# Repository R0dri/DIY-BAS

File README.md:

# DIY - Biosignals Adquisition System with high quality of data adquisition and extremly low cost
This is a DIY EEG device with high quality of the data adquisition, made for research

The data adquisition is made through a Teensy 3.2 board using its 16 bit ADC converters for a good quality. The data is sent through serial com to a raspberry pi 3 for ICA analysis of the data.

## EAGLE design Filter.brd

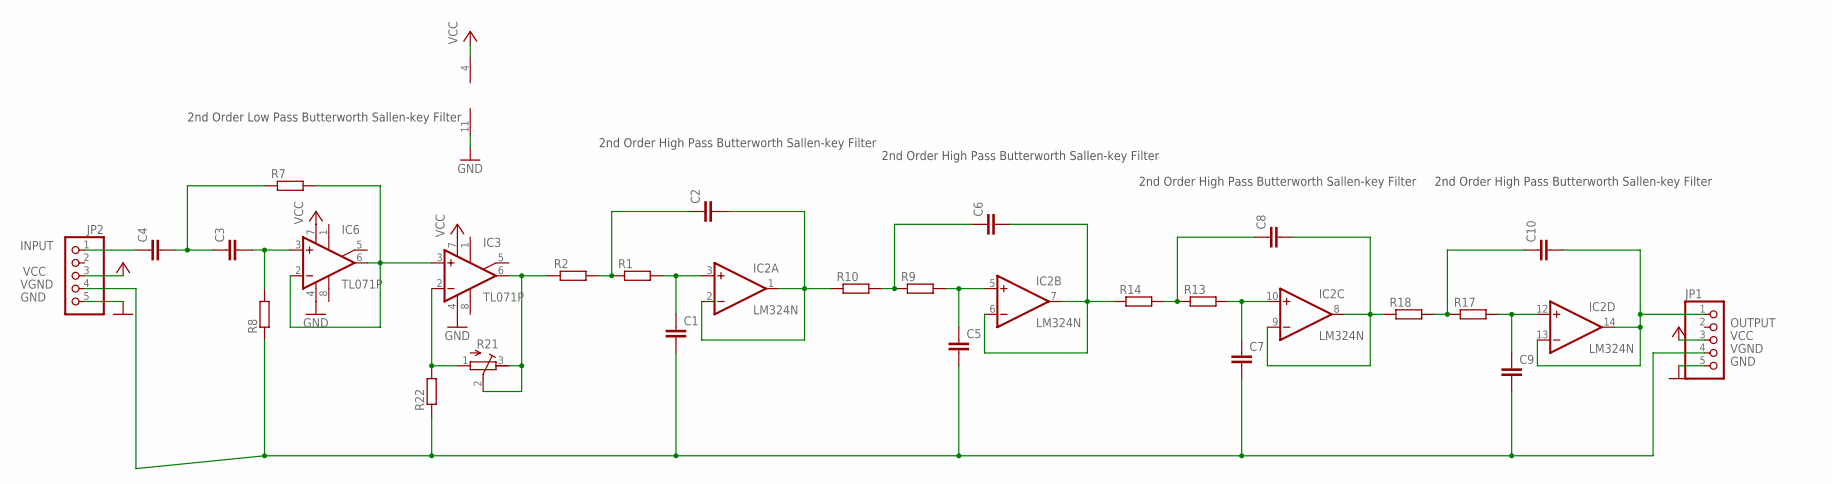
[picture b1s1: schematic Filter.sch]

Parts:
C1, C2, C3, C4, C5, C6, C7, C8, C9, C10: C2.5/2; C2.5-2
IC2: LM324N; DIL14
IC3, IC6: TL071P; DIL08
JP1, JP2: PINHD-1X5; 1X05
R1, R2, R7, R8, R9, R13, R14, R17, R22: R0204/7; 0204/7
R10, R18: R0207/10; 0207/10
R21: R-TRIMM3299W; RTRIM3299W

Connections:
GND: IC2.11 (V-), IC3.4 (V-), IC6.4 (V-), JP1.5, JP2.5
INPUT: C4.1, JP2.1
unnamed: C2.1, R1.1, R2.2
unnamed: C1.1, IC2.3 (+IN), R1.2
unnamed: C2.2, IC2.1 (OUT), IC2.2 (-IN), R10.1
unnamed: IC3.6 (OUT), R2.1, R21.2 (S), R21.3 (E)
unnamed: C3.1, C4.2, R7.1
unnamed: C6.1, R9.1, R10.2
unnamed: C3.2, IC6.3 (+IN), R8.2
unnamed: IC3.3 (+IN), IC6.2 (-IN), IC6.6 (OUT), R7.2
unnamed: C6.2, IC2.6 (-IN), IC2.7 (OUT), R14.1
unnamed: C5.1, IC2.5 (+IN), R9.2
unnamed: C8.1, R13.1, R14.2
unnamed: C8.2, IC2.8 (OUT), IC2.9 (-IN), R18.1
unnamed: C7.1, IC2.10 (+IN), R13.2
unnamed: C10.1, R17.1, R18.2
unnamed: C9.1, IC2.12 (+IN), R17.2
unnamed: IC3.2 (-IN), R21.1 (A), R22.2
OUTPUT: C10.2, IC2.13 (-IN), IC2.14 (OUT), JP1.1
VCC: IC2.4 (V+), IC3.7 (V+), IC6.7 (V+), JP1.3, JP2.3
VGND: C1.2, C5.2, C7.2, C9.2, JP1.4, JP2.4, R8.1, R22.1

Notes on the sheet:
2nd Order Low Pass Butterworth Sallen-key Filter
2nd Order High Pass Butterworth Sallen-key Filter

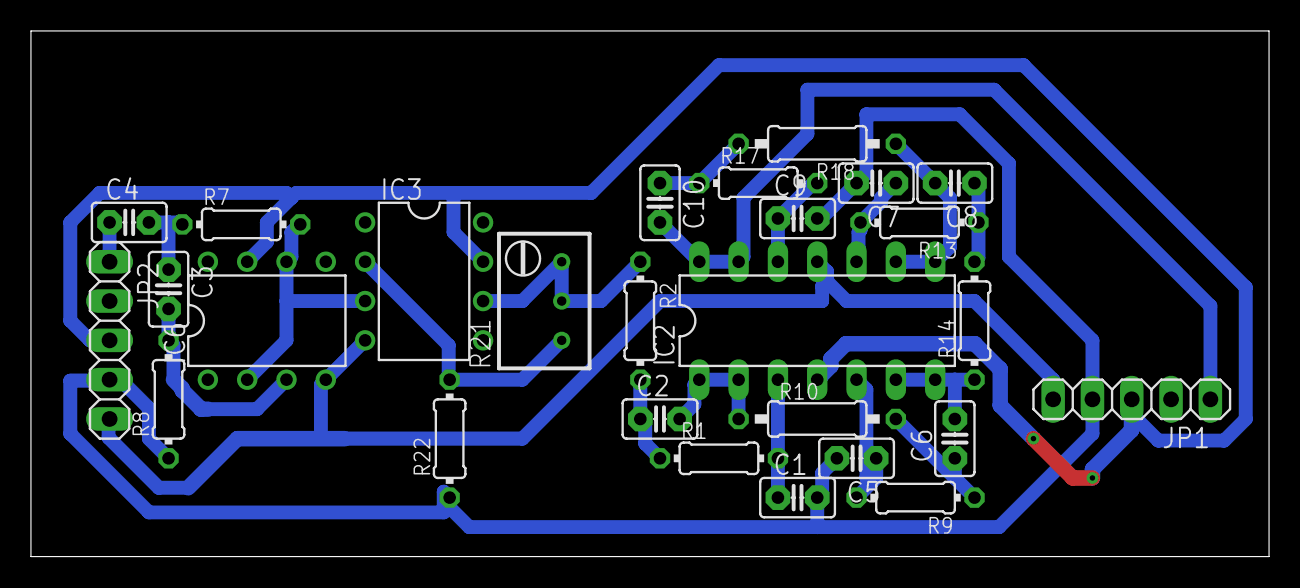
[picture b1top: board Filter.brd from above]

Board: 2 copper layers, 80.0 x 34.0 mm, 27 parts (0 on the bottom side), 21 nets.

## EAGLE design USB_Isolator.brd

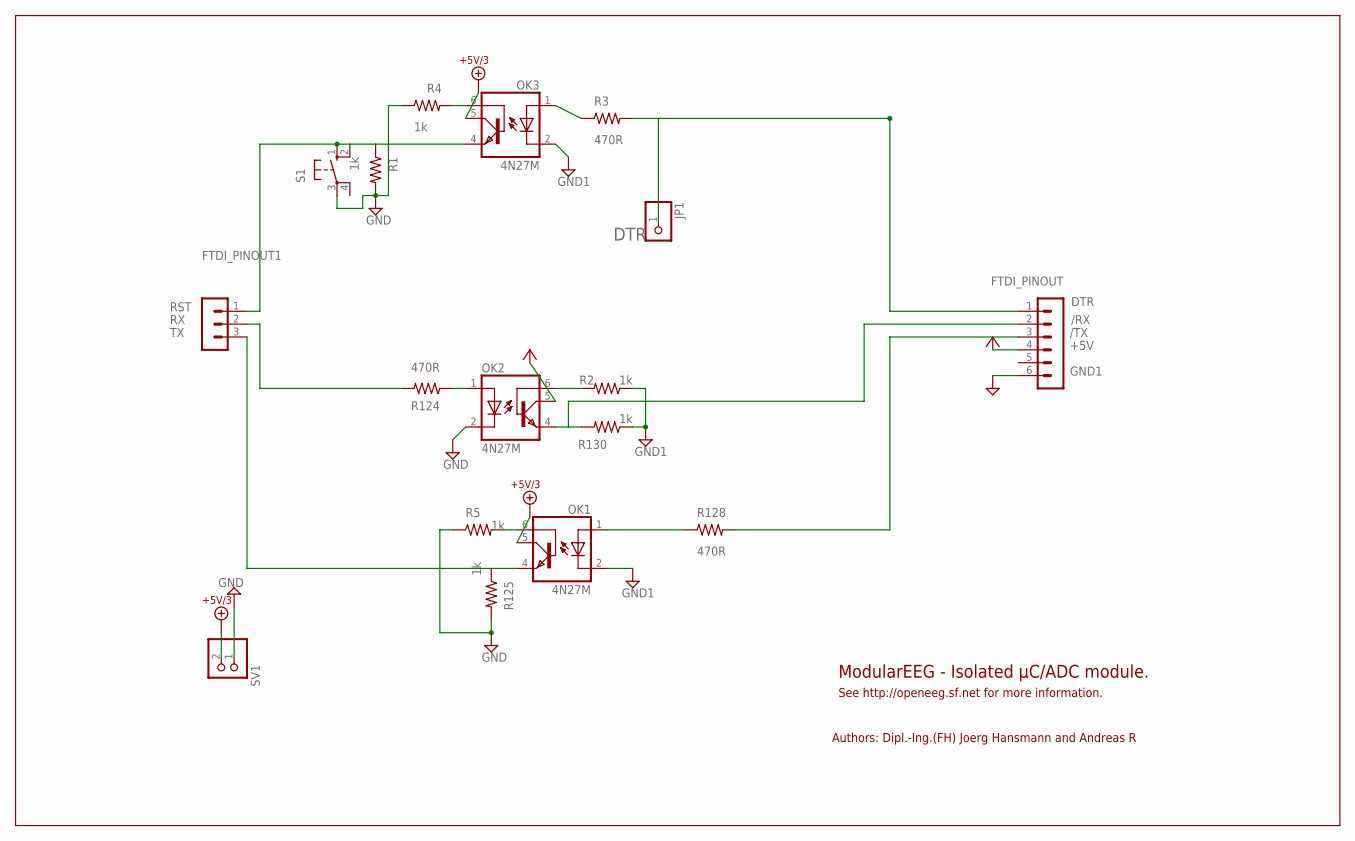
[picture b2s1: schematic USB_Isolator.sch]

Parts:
FTDI_PINOUT: MA06-1
FTDI_PINOUT1: MA03-1
JP1: PINHD-1X1; 1X01
OK1, OK2, OK3: 4N27M; DIL06
R1, R5, R125: 1k; 0204/5
R2, R130: 1k; 0204/7
R3, R124, R128: 470R; 0204/7
R4: 1k; 0204V
S1: 10-XX; B3F-10XX
SV1: PINHD-1X2; 1X02

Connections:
+5V: FTDI_PINOUT.4, OK2.5 (COL)
+5V/3: OK1.5 (COL), OK3.5 (COL), SV1.2
/RX: FTDI_PINOUT.2, OK2.4 (EMI), R130.2
/TX: FTDI_PINOUT.3, R128.2
DTR: FTDI_PINOUT.1, JP1.1, R3.2
GND: OK2.2 (C), R1.2, R4.1, R5.1, R125.2, S1.3, SV1.1
GND1: FTDI_PINOUT.6, OK1.2 (C), OK3.2 (C), R2.1, R130.1
unnamed: OK3.1 (A), R3.1
unnamed: OK2.6 (BAS), R2.2
unnamed: OK3.6 (BAS), R4.2
unnamed: OK1.6 (BAS), R5.2
unnamed: OK2.1 (A), R124.1
unnamed: OK1.1 (A), R128.1
RST: FTDI_PINOUT1.1, OK3.4 (EMI), R1.1, S1.1 (S), S1.2 (S1)
RX: FTDI_PINOUT1.2, R124.2
TX: FTDI_PINOUT1.3, OK1.4 (EMI), R125.1

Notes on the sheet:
Authors: Dipl.-Ing.(FH) Joerg Hansmann and Andreas R
ModularEEG - Isolated µC/ADC module.
See http://openeeg.sf.net for more information.

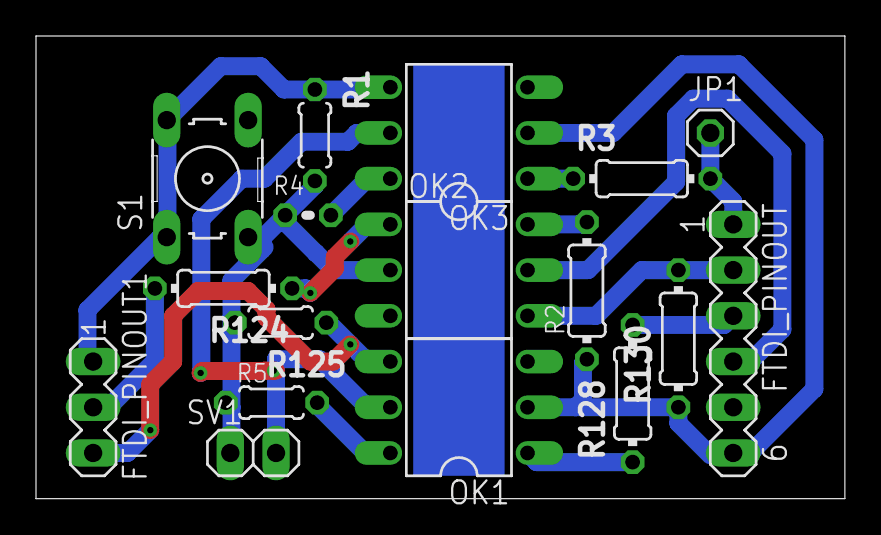
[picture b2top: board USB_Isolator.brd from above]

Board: 2 copper layers, 44.9 x 25.7 mm, 17 parts (0 on the bottom side), 16 nets.

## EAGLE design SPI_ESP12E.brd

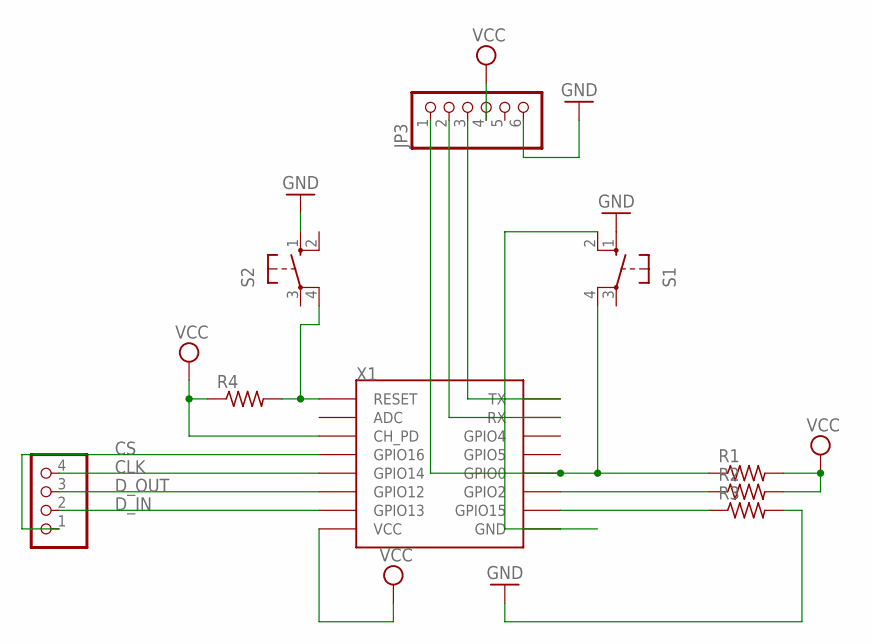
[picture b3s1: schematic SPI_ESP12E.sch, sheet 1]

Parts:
JP3: PINHD-1X6B; 1X06-BIG
R1, R2, R3: R-US_0204/7; 0204/7
R4: R-US_0204/5; 0204/5
S1, S2: 10-XX; B3F-10XX
SPI: PINHD-1X4; 1X04
X1: ESP12SMD; ESP12-SMD

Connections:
CLK: SPI.4, X1.GPIO14
CS: SPI.1, X1.GPIO16
D_IN: SPI.2, X1.GPIO13
D_OUT: SPI.3, X1.GPIO12
GND: JP3.6, R3.2, S1.1 (S), S2.1 (S)
unnamed: R3.1, X1.GPIO15
unnamed: S1.2 (S1), X1.GND
unnamed: R2.1, X1.GPIO2
unnamed: R4.2, S2.4 (P1), X1.RESET
unnamed: JP3.1, R1.1, S1.4 (P1), X1.GPIO0
unnamed: JP3.3, X1.TXD0 (TX)
unnamed: JP3.2, X1.RXD0 (RX)
VCC: JP3.4, R1.2, R2.2, R4.1, X1.CH_PD, X1.VCC

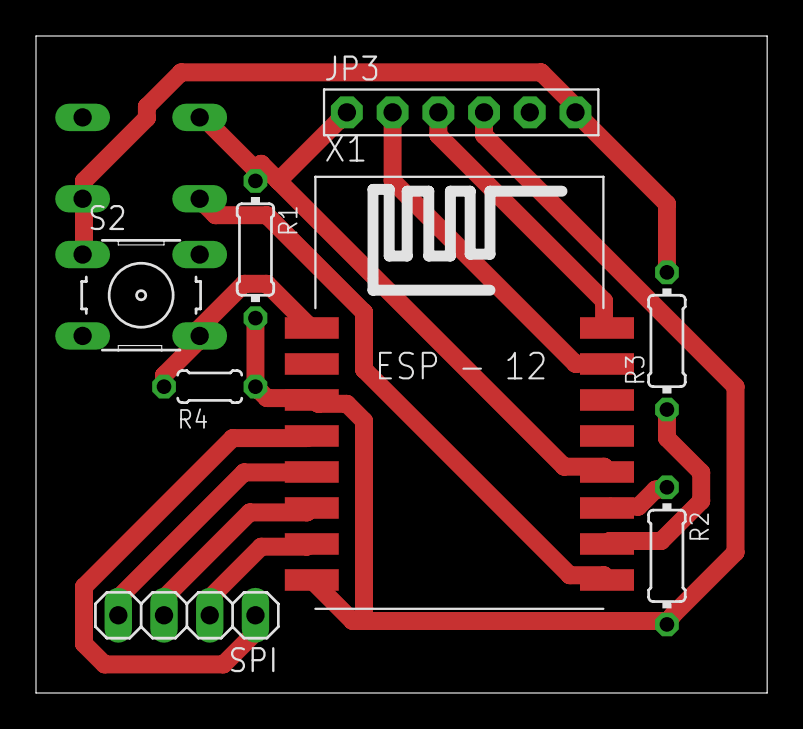
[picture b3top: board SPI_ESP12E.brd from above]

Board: 2 copper layers, 40.6 x 36.5 mm, 9 parts (1 on the bottom side), 13 nets.

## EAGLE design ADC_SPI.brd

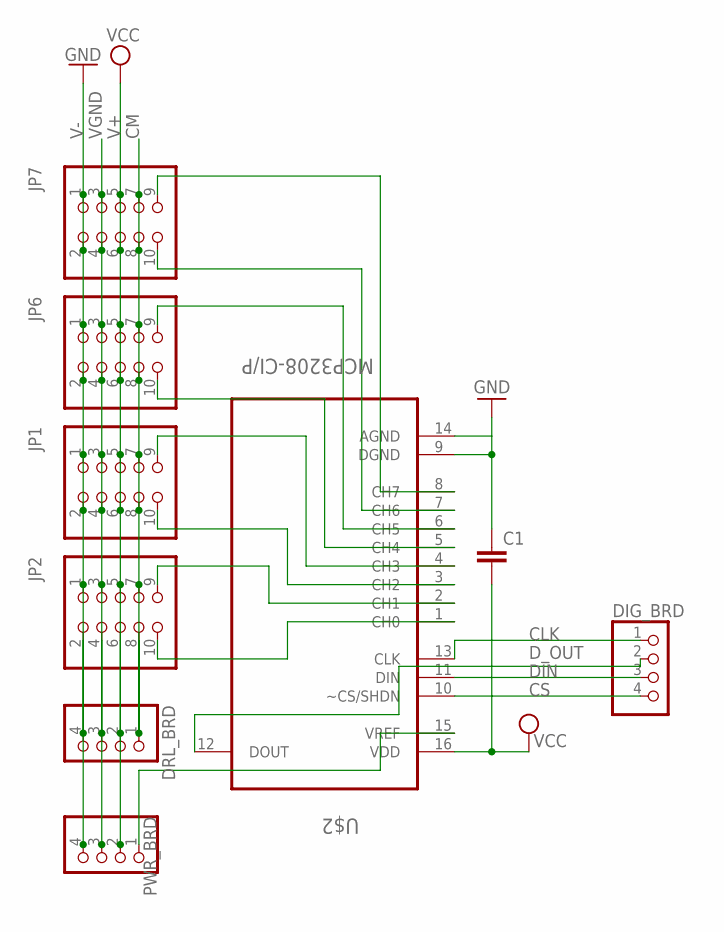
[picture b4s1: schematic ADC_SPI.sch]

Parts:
C1: C2.5/2; C2.5-2
DIG_BRD: PINHD-1X4; 1X04
DRL_BRD: PINHD-1X4; 1X04
JP1, JP2, JP6, JP7: PINHD-2X5; 2X05
PWR_BRD: PINHD-1X4; 1X04
U$2: MCP3208-CI/P; DIP254P762X432-16

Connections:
CLK: DIG_BRD.1, U$2.13 (CLK)
CM: DRL_BRD.1, JP1.7, JP1.8, JP2.7, JP2.8, JP6.7, JP6.8, JP7.7, JP7.8
CS: DIG_BRD.4, U$2.10 (~CS/SHDN)
DIN: DIG_BRD.3, U$2.11 (DIN)
D_OUT: DIG_BRD.2, U$2.12 (DOUT)
GND: C1.1, U$2.9 (DGND), U$2.14 (AGND)
unnamed: JP2.10, U$2.1 (CH0)
unnamed: PWR_BRD.1, U$2.15 (VREF)
unnamed: JP7.9, U$2.8 (CH7)
unnamed: JP7.10, U$2.7 (CH6)
unnamed: JP6.9, U$2.6 (CH5)
unnamed: JP6.10, U$2.5 (CH4)
unnamed: JP1.9, U$2.4 (CH3)
unnamed: JP1.10, U$2.3 (CH2)
unnamed: JP2.9, U$2.2 (CH1)
V+: DRL_BRD.2, JP1.5, JP1.6, JP2.5, JP2.6, JP6.5, JP6.6, JP7.5, JP7.6, PWR_BRD.2
V-: DRL_BRD.4, JP1.1, JP1.2, JP2.1, JP2.2, JP6.1, JP6.2, JP7.1, JP7.2, PWR_BRD.4
VCC: C1.2, U$2.16 (VDD)
VGND: DRL_BRD.3, JP1.3, JP1.4, JP2.3, JP2.4, JP6.3, JP6.4, JP7.3, JP7.4, PWR_BRD.3

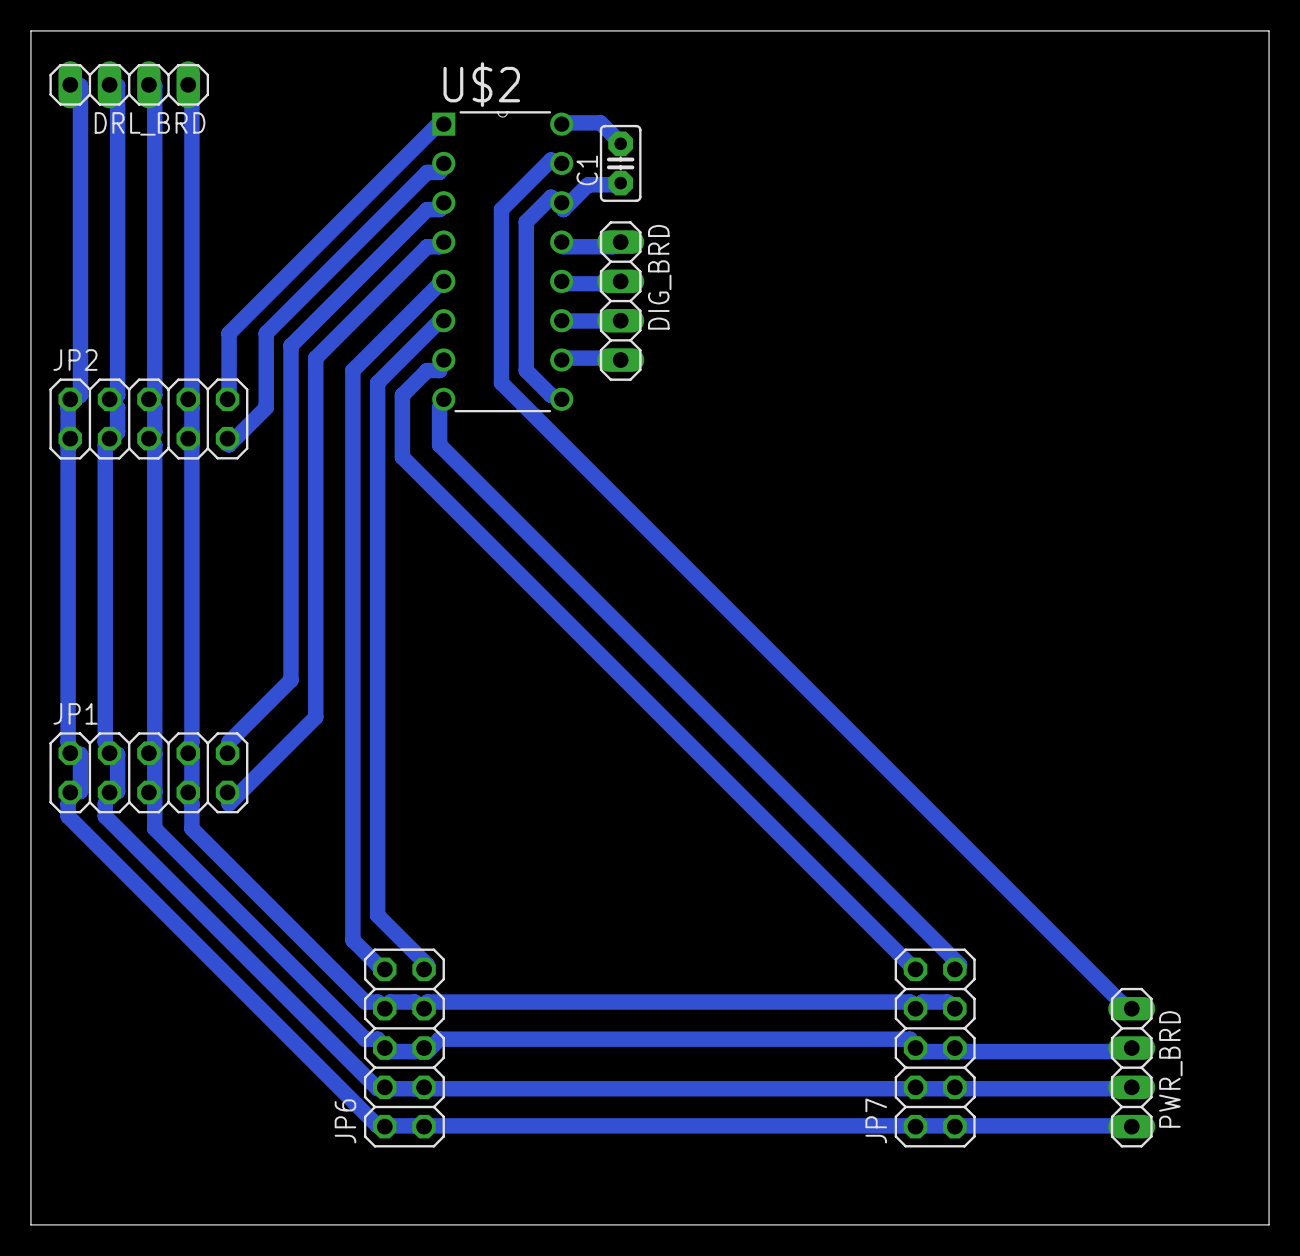
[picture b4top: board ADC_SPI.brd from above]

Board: 2 copper layers, 80.0 x 77.1 mm, 9 parts (0 on the bottom side), 19 nets.

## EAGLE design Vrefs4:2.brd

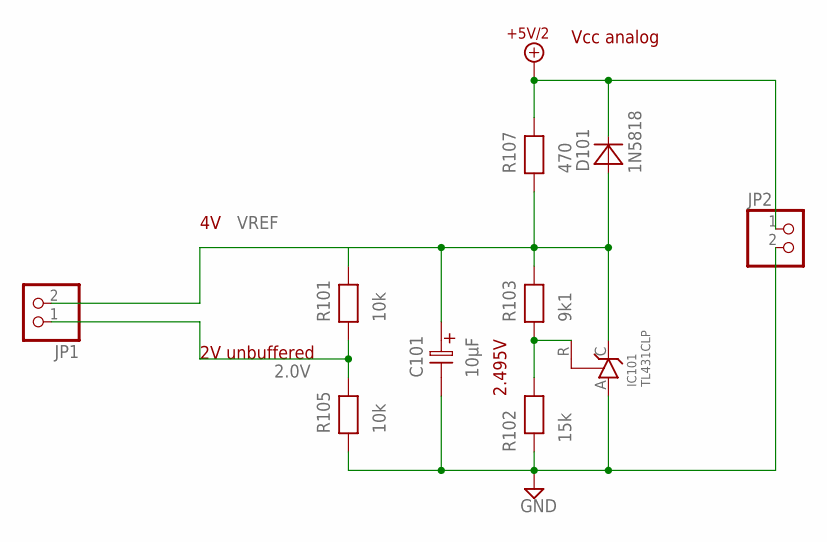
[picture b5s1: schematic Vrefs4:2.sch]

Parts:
C101: 10µF; EL25B
D101: 1N5818; D-10
IC101: TL431CLP; TO92-CLP
JP1, JP2: PINHD-1X2; 1X02
R101, R105: 10k; R-10
R102: 15k; R-10
R103: 9k1; R-10
R107: 470; R-10

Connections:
2.0V: JP1.1, R101.1, R105.2
+5V/2: D101.2 (K), JP2.1, R107.2
GND: C101.2, IC101.A, JP2.2, R102.1, R105.1
unnamed: IC101.R, R102.2, R103.1
VREF: C101.1, D101.1 (A), IC101.C, JP1.2, R101.2, R103.2, R107.1

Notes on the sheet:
2.495V
2V unbuffered
Vcc analog

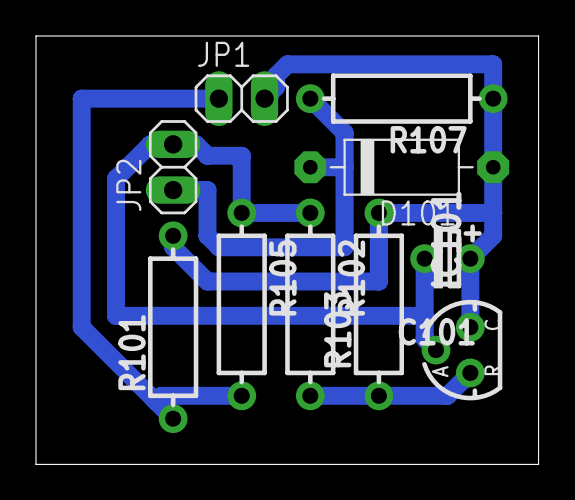
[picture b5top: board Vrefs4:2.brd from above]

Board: 2 copper layers, 27.9 x 23.8 mm, 10 parts (0 on the bottom side), 5 nets.

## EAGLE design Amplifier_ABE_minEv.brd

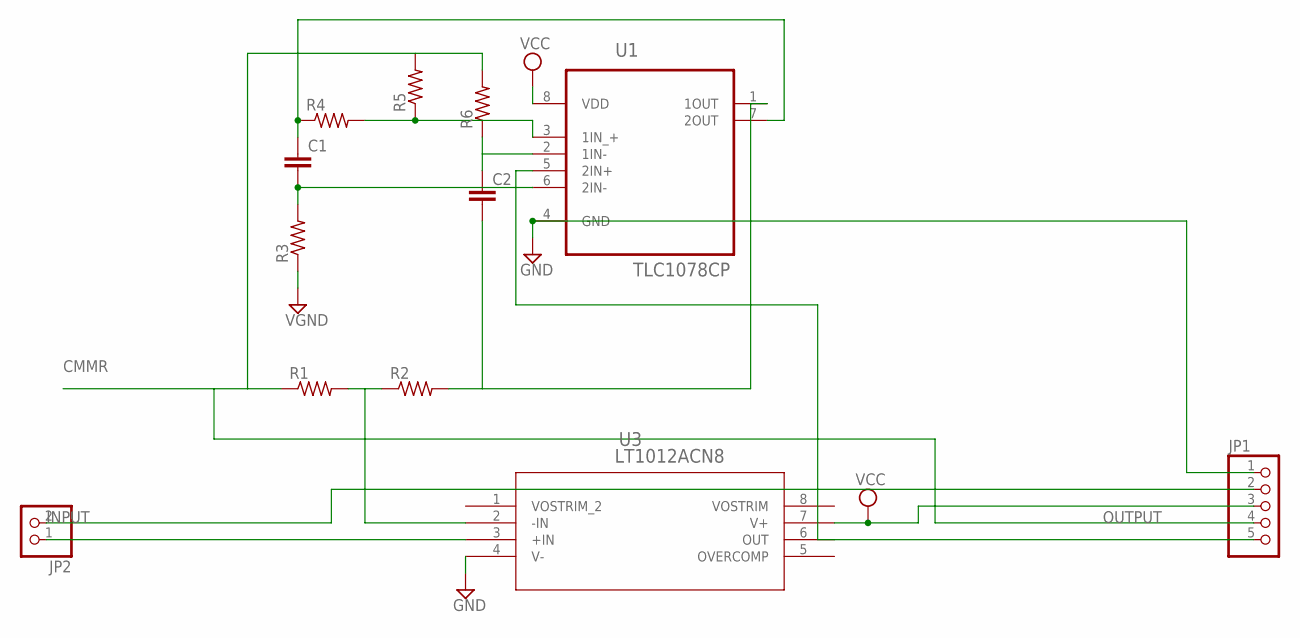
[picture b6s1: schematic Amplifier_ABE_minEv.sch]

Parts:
C1, C2: C-EU025-024X044; C025-024X044
JP1: PINHD-1X5; 1X05
JP2: PINHD-1X2; 1X02
R1, R2, R4, R5: R-US_0204/7; 0204/7
R3, R6: R-US_0204/5; 0204/5
U1: TLC1078CP; DIP254P762X508-8
U3: LT1012ACN8; LT1012ACN8_PDIP-8_N

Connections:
CMMR: JP1.4, R1.1, R5.2, R6.2
GND: JP1.1, R3.1, U1.4 (GND), U3.4 (V-)
INPUT: JP2.1, U3.3 (+IN)
unnamed: R1.2, R2.1, U3.2 (-IN)
unnamed: JP1.2, JP2.2
unnamed: C2.2, R2.2, U1.1 (1OUT)
unnamed: C1.2, R3.2, U1.6 (2IN-)
unnamed: C1.1, R4.1, U1.7 (2OUT)
unnamed: R4.2, R5.1, U1.3 (1IN_+)
unnamed: C2.1, R6.1, U1.2 (1IN-)
OUTPUT: JP1.5, U1.5 (2IN+), U3.6 (OUT)
VCC: JP1.3, U1.8 (VDD), U3.7 (V+)

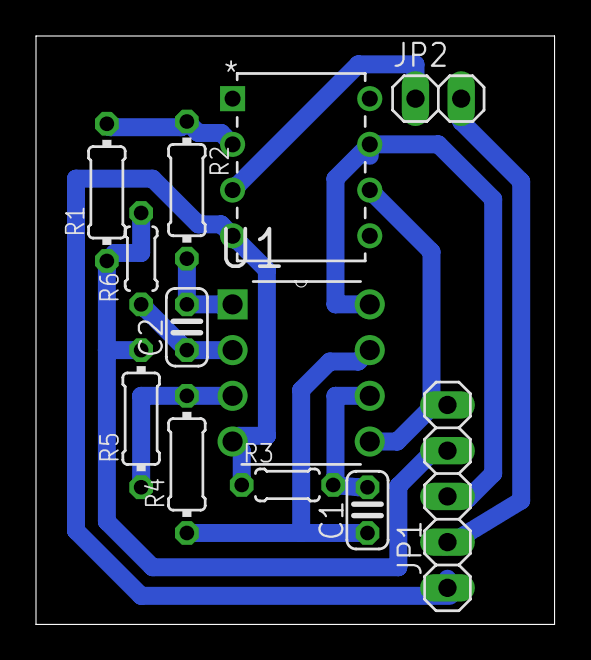
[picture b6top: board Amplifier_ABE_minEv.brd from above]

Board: 2 copper layers, 28.8 x 32.7 mm, 12 parts (0 on the bottom side), 12 nets.

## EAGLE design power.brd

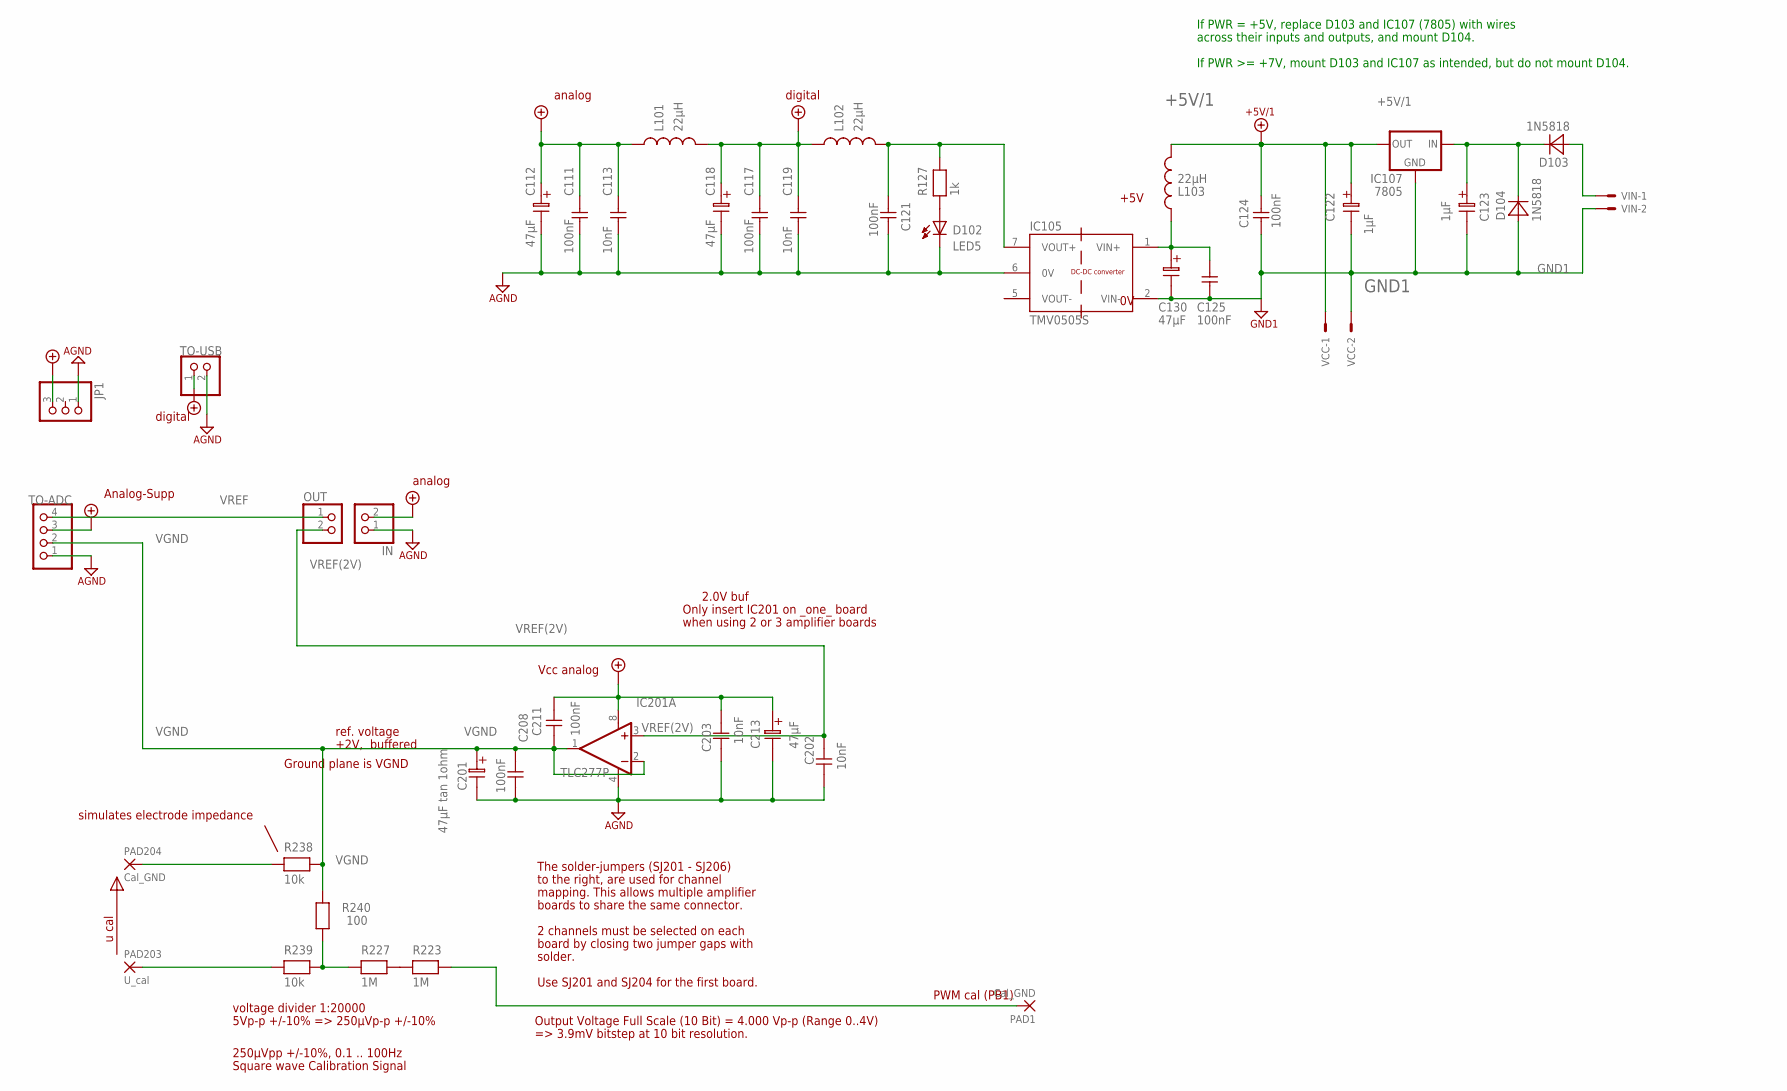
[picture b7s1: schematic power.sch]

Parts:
C111, C117, C125, C208, C211: 100nF; C-5
C112, C118, C130, C213: 47µF; EL25B
C113, C119, C202, C203: 10nF; C-5
C121, C124: 100nF; C-5@1
C122, C123: 1µF; EL25B
C201: 47µF tan 1ohm; EL25B
D102: LED5
D103, D104: 1N5818; D-12,5
IC105: TMV0505S; MEJDCDC-SC
IC107: 7805; 78XXL_S
IC201: TLC277P; DIL-08
IN: PINHD-1X2; 1X02
JP1: PINHD-1X3; 1X03
L101, L102, L103: 22µH; R-12,5
OUT: PINHD-1X2; 1X02
PAD1, PAD204: Cal_GND; WIREPAD1
PAD203: U_cal; WIREPAD1
R127: 1k; R-10
R223, R227: 1M; R-10
R238, R239: 10k; R-10
R240: 100; R-10
TO-ADC: PINHD-1X4; 1X04
TO-USB: PINHD-1X2; 1X02
VCC: 87758-0216
VIN: 22-23-2021

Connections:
+5V/1: C122.1, C124.2, IC107.OUT, L103.2, VCC.1
+6TO12V: C123.1, D103.2 (K), D104.2 (K), IC107.IN
A-VCC: C111.2, C112.1, C113.2, C203.1, C211.2, C213.1, IC201.8 (V+), IN.2, L101.1, TO-ADC.3
D-VCC: C117.2, C118.1, C119.2, JP1.3, L101.2, L102.1, TO-USB.1
GND: C111.1, C112.2, C113.1, C117.1, C118.2, C119.1, C121.2, C201.2, C202.2, C203.2, C208.2, C213.2, D102.K, IC105.6 (0V), IC201.4 (V-), IN.1, JP1.1, TO-ADC.1, TO-USB.2
GND1: C122.2, C123.2, C124.1, C125.1, C130.2, D104.1 (A), IC105.2 (VIN-), IC107.GND, VCC.2, VIN.2
unnamed: C121.1, IC105.7 (VOUT+), L102.2, R127.2
unnamed: D102.A, R127.1
unnamed: D103.1 (A), VIN.1
unnamed: PAD204.1, R238.1
unnamed: R227.1, R239.2, R240.2
unnamed: C125.2, C130.1, IC105.1 (VIN+), L103.1
unnamed: R223.1, R227.2
unnamed: PAD203.1, R239.1
PWM: PAD1.1, R223.2
VGND: C201.1, C208.1, C211.1, IC201.1 (OUT), IC201.2 (-IN), R238.2, R240.1, TO-ADC.2
VOUT-: IC105.5 (VOUT-)
VREF: OUT.1, TO-ADC.4
VREF(2V): C202.1, IC201.3 (+IN), OUT.2

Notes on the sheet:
+5V
analog
digital
If PWR = +5V, replace D103 and IC107 (7805) with wires
If PWR >= +7V, mount D103 and IC107 as intended, but do not mount D104.
across their inputs and outputs, and mount D104.
ref. voltage
+2V, buffered
u cal
Output Voltage Full Scale (10 Bit) = 4.000 Vp-p (Range 0..4V)
Vcc analog
2.0V buf
PWM cal (PB1)
250µVpp +/-10%, 0.1 .. 100Hz
Square wave Calibration Signal
voltage divider 1:20000
simulates electrode impedance
Ground plane is VGND
5Vp-p +/-10% => 250µVp-p +/-10%
when using 2 or 3 amplifier boards
Only insert IC201 on _one_ board
The solder-jumpers (SJ201 - SJ206)
boards to share the same connector.
2 channels must be selected on each
solder.
to the right, are used for channel
mapping. This allows multiple amplifier
=> 3.9mV bitstep at 10 bit resolution.
board by closing two jumper gaps with
Use SJ201 and SJ204 for the first board.
Analog-Supp

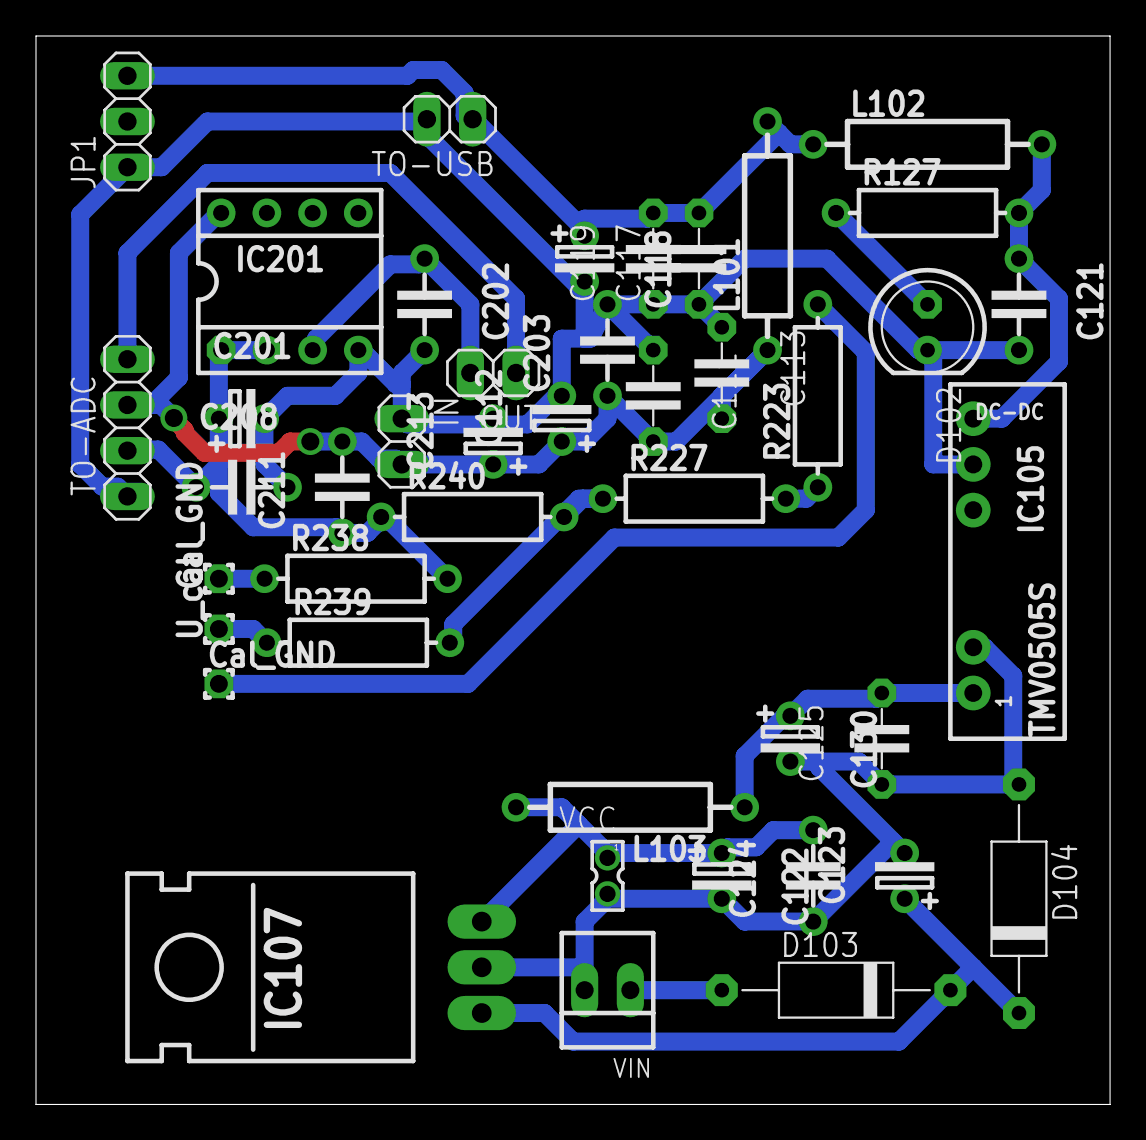
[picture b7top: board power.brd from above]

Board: 2 copper layers, 59.7 x 59.4 mm, 43 parts (0 on the bottom side), 18 nets.

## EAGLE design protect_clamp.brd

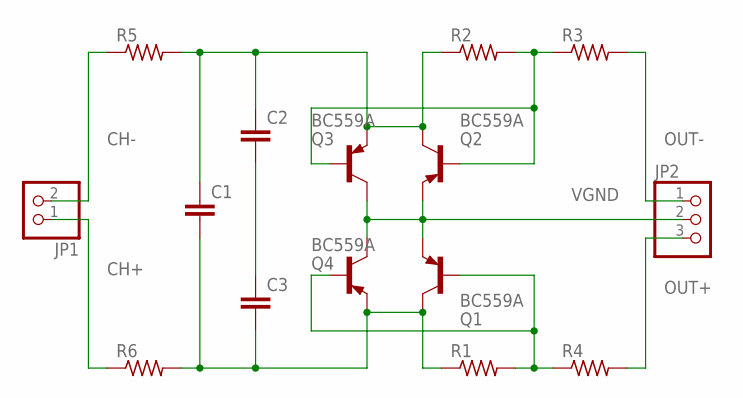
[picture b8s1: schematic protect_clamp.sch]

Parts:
C1, C2, C3: C2.5/2; C2.5-2
JP1: PINHD-1X2; 1X02
JP2: PINHD-1X3; 1X03
Q1, Q2, Q3, Q4: BC559A; TO92-EBC
R1, R2, R3, R4, R5, R6: R-US_0204/5; 0204/5

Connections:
CH+: JP1.1, R6.1
CH-: JP1.2, R5.1
unnamed: Q1.B, Q4.B, R1.2, R4.1
unnamed: Q2.B, Q3.B, R2.2, R3.1
unnamed: C2.2, C3.1
unnamed: C1.2, C3.2, Q1.C, Q4.E, R1.1, R6.2
unnamed: C1.1, C2.1, Q2.C, Q3.E, R2.1, R5.2
OUT+: JP2.3, R4.2
OUT-: JP2.1, R3.2
VGND: JP2.2, Q1.E, Q2.E, Q3.C, Q4.C

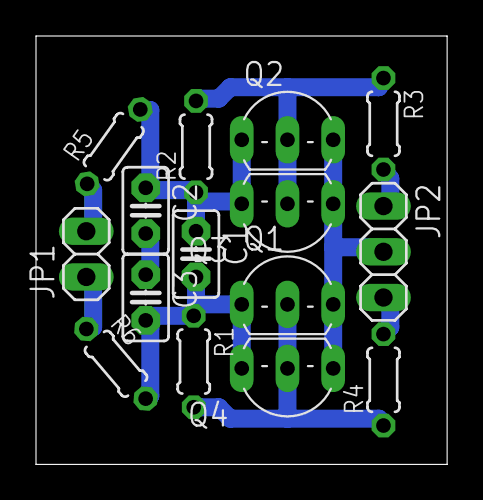
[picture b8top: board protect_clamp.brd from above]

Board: 2 copper layers, 22.8 x 23.8 mm, 15 parts (0 on the bottom side), 10 nets.

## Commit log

2017-01-02 Changes to be committed: modified: README.md new file: test.txt
2017-01-02 Changes to be committed: deleted: test.txt
2017-01-02 Changes to be committed: modified: README.md

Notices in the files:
parts and their libraries:
COPYRIGHT: Copyright C 2016 Accelerated Designs. All rights reserved
